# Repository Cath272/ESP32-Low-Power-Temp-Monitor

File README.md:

# ESP32 Low Power Temp Monitor

## Introduction
ESP32 Low Power Temp Monitor is an ESP32 C6 based low power Temperature and Humidity Monitor that aims to have a device that is very efficent and doen't need charging.
## General description
The device reads the temperature, relative humidity and barometric pressure  and displays it on an 4.2 inch Epaper Display, alonside the current date and time.
The device is awake just for a few seconds as it reads the tempereature and displays it and then goes to sleep. It performs a reading every minute.
One a day it connects to WiFi and checks the current time to sync up with an NTP server to account for Daylight saving time and potential drifts in the internal esp32 real time clock.

In the project files you may find ESP32-C3 instead of ESP32-C6. I named it wrong when i created the project. The issue is just the file names, the footprints are correct and use a C6.
The TPL5111 is currenly does not work properly so i emulated it in software using the esp32 deep sleep.

### Block diagram

## Hardware Design
### ESP32 C6 Wroom 1 Module
This project is based around a ESP32 C6 Wroom 1 Module that incorporates a RISC-V single-core microprocessor with 4MB of flash, WiFi 6 and Zigbee
### TPS63020
The TPS63020 is High Efficiency Single Inductor Buck-Boost Converter, used for  converting the 5v from usb or the Li-ion battery voltage(3.0v to 4.2v) to a very stable 3.3V for the Microcontroller and the epaper display. The main advantage of this ic is its low operating quiescent current: 25 μA; and it's low cost:0.55€
### BME280
The BME280 is a digital humidity, pressure and temperature sensor.
### 4.2 Inch Epaper Display 
GDEY042Z98 Tri color (Black, White and Red) Epaper display using a SSD1683 driver chip, the main benefit of this display is its big size (4.2 inch) and very good price for an Epaper display (around 10€)
### TPL5111
The TPL5111 is a Nano Power System timer for power gating. It is used to turn on the esp32 every minute to read the temperature
### MCP7381
The MCP7381 is an integrated Li-ion cell battery controller 
### Li-ion 250MAh battery
Small 250Mah generic Li-ion cell with protection, used because of its small size
### Solar Panel
Generic 1W 5V Solar panel 

## Schematic
[Schematic](PCB/ESP32%20%20C3%20Zigbee%20Temp/ESP32%20%20C3%20Zigbee%20Temp.pdf)
## Bill of Materials

| Component           |         Image                                                                                         |         Model  |           Pcs | Price           | 
| -------------       |                                                                                        -------------  | -------------  | ------------- | --------------- |
| ESP32-C6-WROOM-1-N8  |          | ESP32-C6-WROOM-1-N8 | 1             | € 4.91          |
|Buck Boost Coverter  |        |   TPS63020     | 1             | € 0.52          | 
| TPL5111        |             | TPL5111         | 1             | € 0.47       |     
| BME280        |             | BME280         | 1             | € 2.78      |
| MCP7381        |             | MCP7381         | 1             | € 0.84      |
| Solar Panel        |             | 5V 1W Solar Panel         | 1             | € 2.23       |
| 4.2 Inch Epaper Display |             | GDEY042Z98         | 1             | € 11.64       |

## PCB

## Case and 3d design

The case was make using autocad and exported to stl
The stl files can be found in the 3D Parts folder

The gerber production zip file can be found in the Production folder
## Software Design

The device wakes up, connect to wifi on the first boot, reads the time from an NTP server, and then for the next 24 hours it just reads the temperature and displays it. The time is kept in a register while the esp sleeps and increments it on every boot. Every 24 hours it connect to Wifi to check the time again for accuracy.
The program can be found in the Project_Code folder

### Display
The program is based around the [GxEPD2](https://github.com/ZinggJM/GxEPD2) libary for interfacing with the Epaper display,   

### Fonts
The font used in this project is Roboto with 2 diffrent font sizes: 16pt for the time, date, altitude and barometric pressure and 48pt for the Temeprature and relative humidity
The font were converted from True Type to Adafruit's GFX Font format (also used by GxEPD2 as it is based on Adafruit GFX) using the [ttf2gfx utility](https://github.com/Pconti31/TTF2GFX)

### BME280
Adafruit_BME280 for the BME280 sensor
### Time 
For time i used 4 libraries: 
- esp_timer (esp_idf library) to get the execution time of the code 
- [ESP32Time](https://github.com/fbiego/ESP32Time) for keeeping the time and displaying it in a C style format on the display
- [ezTime](https://github.com/ropg/ezTime) for getting the time from an NTP server, the time is region based in this library and i used it to avoid the problem of keeping track of daylight savings

## Results

## Resources
- [ESP32Time](https://github.com/fbiego/ESP32Time)
- [ttf2gfx utility](https://github.com/Pconti31/TTF2GFX)
- [ezTime](https://github.com/ropg/ezTime)
- [GxEPD2](https://github.com/ZinggJM/GxEPD2)

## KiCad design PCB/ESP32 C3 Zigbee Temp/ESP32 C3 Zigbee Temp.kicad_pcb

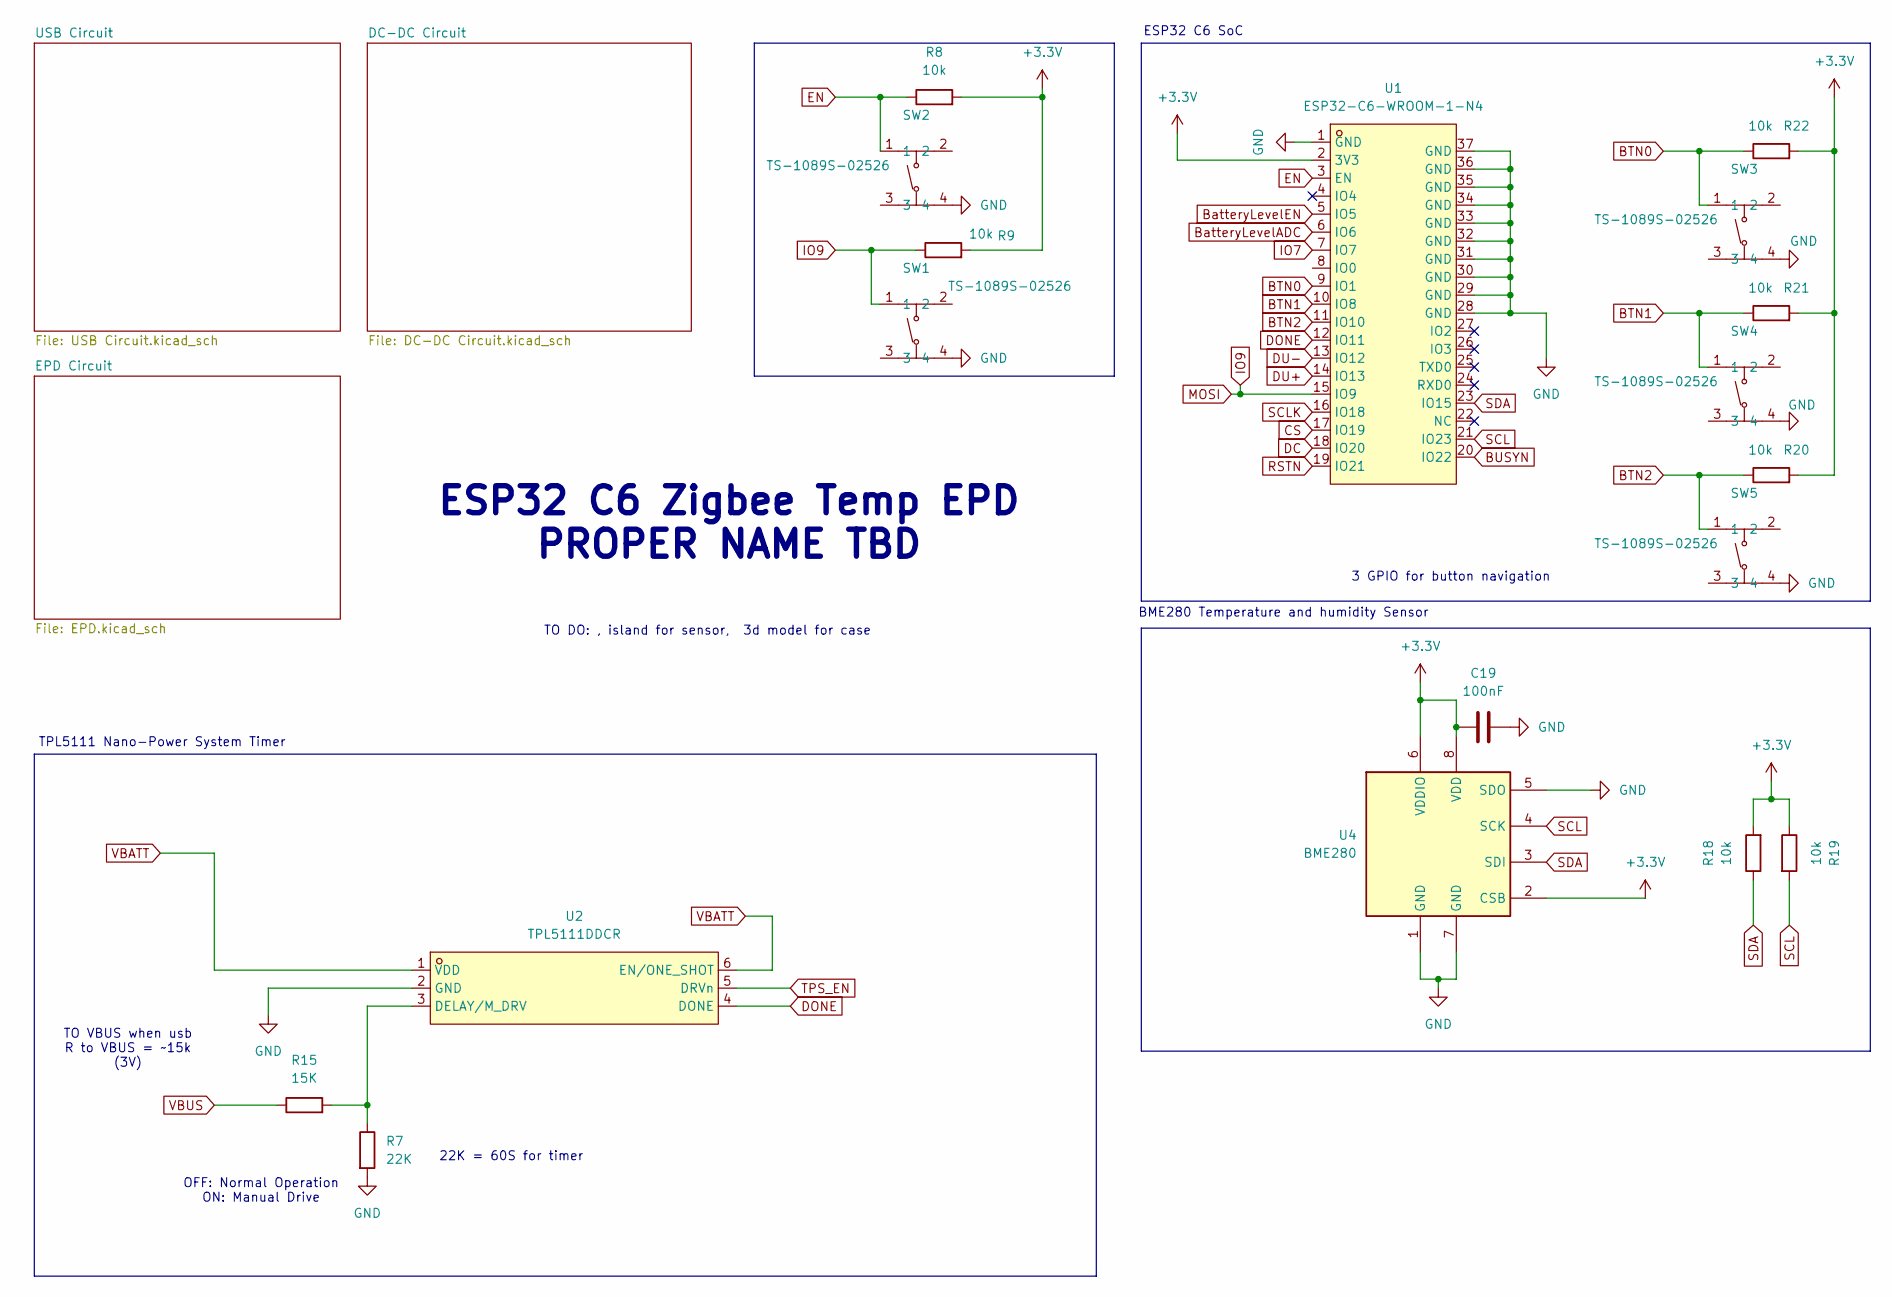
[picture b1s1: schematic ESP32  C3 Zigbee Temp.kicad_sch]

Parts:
C19: 100nF; C_0402_1005Metric
R7: 22K; R_0402_1005Metric
R8, R9, R18, R19, R20, R21, R22: 10k; R_0402_1005Metric
R15: 15K; R_0402_1005Metric
SW1, SW2, SW3, SW4, SW5: TS-1089S-02526; SW-SMD_4P-L4.2-W3.3-P2.15-LS5.1; LCSC Part C455282
U1: ESP32-C6-WROOM-1-N4; WIRELM-SMD_ESP32-C6-WROOM-1; LCSC Part C6034714
U2: TPL5111DDCR; TSOT-23-6_L2.9-W1.6-P0.95-LS2.8-BL; LCSC Part C2870554
U4: BME280; Bosch_LGA-8_2.5x2.5mm_P0.65mm_ClockwisePinNumbering

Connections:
+3.3V: C19.1, R8.2, R9.2, R18.2, R19.1, R20.2, R21.2, R22.2, U1.2 (3V3), U4.2 (CSB), U4.6 (VDDIO), U4.8 (VDD); also elsewhere on the board
BTN0: R22.1, SW3.1, U1.9 (IO1)
BTN1: R21.1, SW4.1, U1.10 (IO8)
BTN2: R20.1, SW5.1, U1.11 (IO10)
BUSYN: U1.20 (IO22); also elsewhere on the board
BatteryLevelADC: U1.6 (IO6); also elsewhere on the board
BatteryLevelEN: U1.5 (IO5); also elsewhere on the board
CS: U1.17 (IO19); also elsewhere on the board
DC: U1.18 (IO20); also elsewhere on the board
DONE: U1.12 (IO11), U2.4 (DONE)
DU+: U1.14 (IO13); also elsewhere on the board
DU-: U1.13 (IO12); also elsewhere on the board
EN: R8.1, SW2.1, U1.3 (EN)
GND: C19.2, R7.2, SW1.4, SW2.4, SW3.4, SW4.4, SW5.4, U1.1 (GND), U1.28 (GND), U1.29 (GND), U1.30 (GND), U1.31 (GND), U1.32 (GND), U1.33 (GND), U1.34 (GND), U1.35 (GND), U1.36 (GND), U1.37 (GND), U2.2 (GND), U4.1 (GND), U4.5 (SDO), U4.7 (GND); also elsewhere on the board
IO7: U1.7 (IO7); also elsewhere on the board
IO9: R9.1, SW1.1, U1.15 (IO9); also elsewhere on the board
unnamed: R7.1, R15.2, U2.3 (DELAY/M_DRV)
RSTN: U1.19 (IO21); also elsewhere on the board
SCL: R19.2, U1.21 (IO23), U4.4 (SCK)
SCLK: U1.16 (IO18); also elsewhere on the board
SDA: R18.1, U1.23 (IO15), U4.3 (SDI)
TPS_EN: U2.5 (DRVn); also elsewhere on the board
VBATT: U2.1 (VDD), U2.6 (EN/ONE_SHOT); also elsewhere on the board
VBUS: R15.1; also elsewhere on the board

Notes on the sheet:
ESP32 C6 SoC
OFF: Normal Operation ON: Manual Drive
3 GPIO for button navigation
TO DO: , island for sensor, 3d model for case
TO VBUS when usb R to VBUS = ~15k (3V)
TPL5111 Nano-Power System Timer
ESP32 C6 Zigbee Temp EPD PROPER NAME TBD
22K = 60S for timer
BME280 Temperature and humidity Sensor

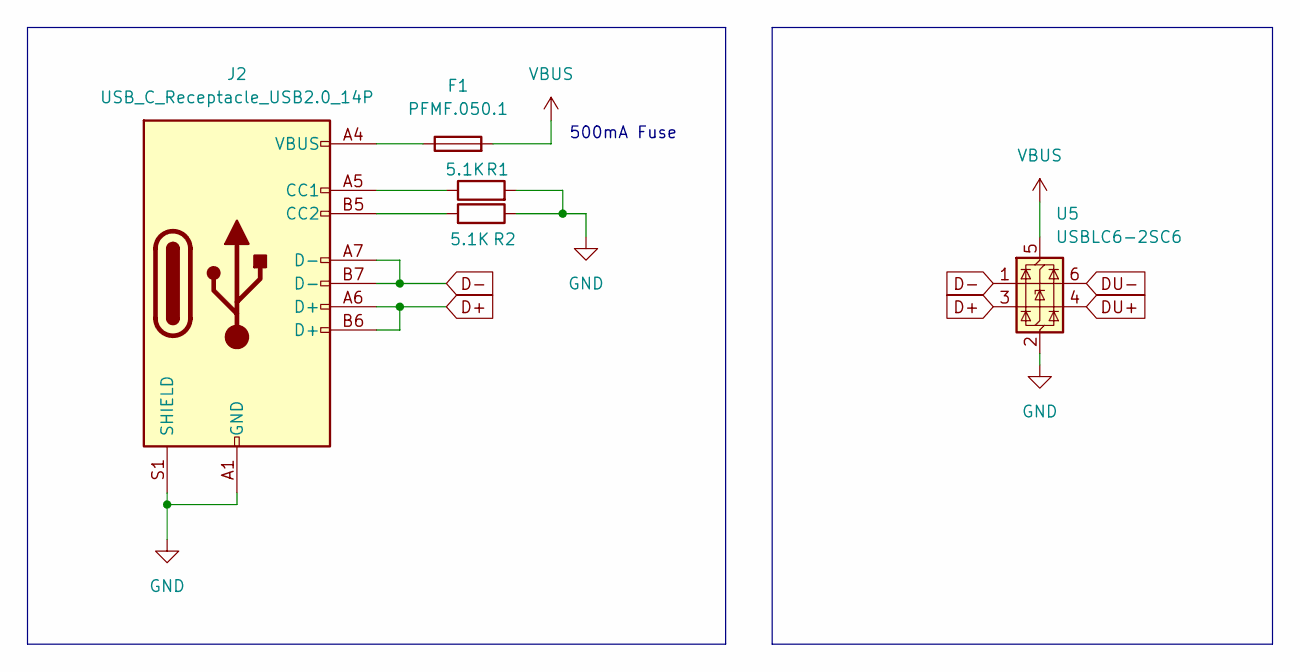
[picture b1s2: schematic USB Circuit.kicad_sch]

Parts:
F1: PFMF.050.1; Fuse_1812_4532Metric
J2: USB_C_Receptacle_USB2.0_14P; USB_C_Receptacle_GCT_USB4110
R1, R2: 5.1K; R_0402_1005Metric
U5: USBLC6-2SC6; SOT-23-6

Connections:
D+: J2.A6 (D+), J2.B6 (D+), U5.3 (I/O2)
D-: J2.A7 (D-), J2.B7 (D-), U5.1 (I/O1)
DU+: U5.4 (I/O2); also elsewhere on the board
DU-: U5.6 (I/O1); also elsewhere on the board
GND: J2.A1 (GND), J2.A12 (GND), J2.B1 (GND), J2.B12 (GND), J2.S1 (SHIELD), R1.2, R2.1, U5.2 (GND); also elsewhere on the board
unnamed: F1.1, J2.A4 (VBUS), J2.A9 (VBUS), J2.B4 (VBUS), J2.B9 (VBUS)
unnamed: J2.A5 (CC1), R1.1
unnamed: J2.B5 (CC2), R2.2
VBUS: F1.2, U5.5 (VBUS); also elsewhere on the board

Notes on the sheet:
500mA Fuse

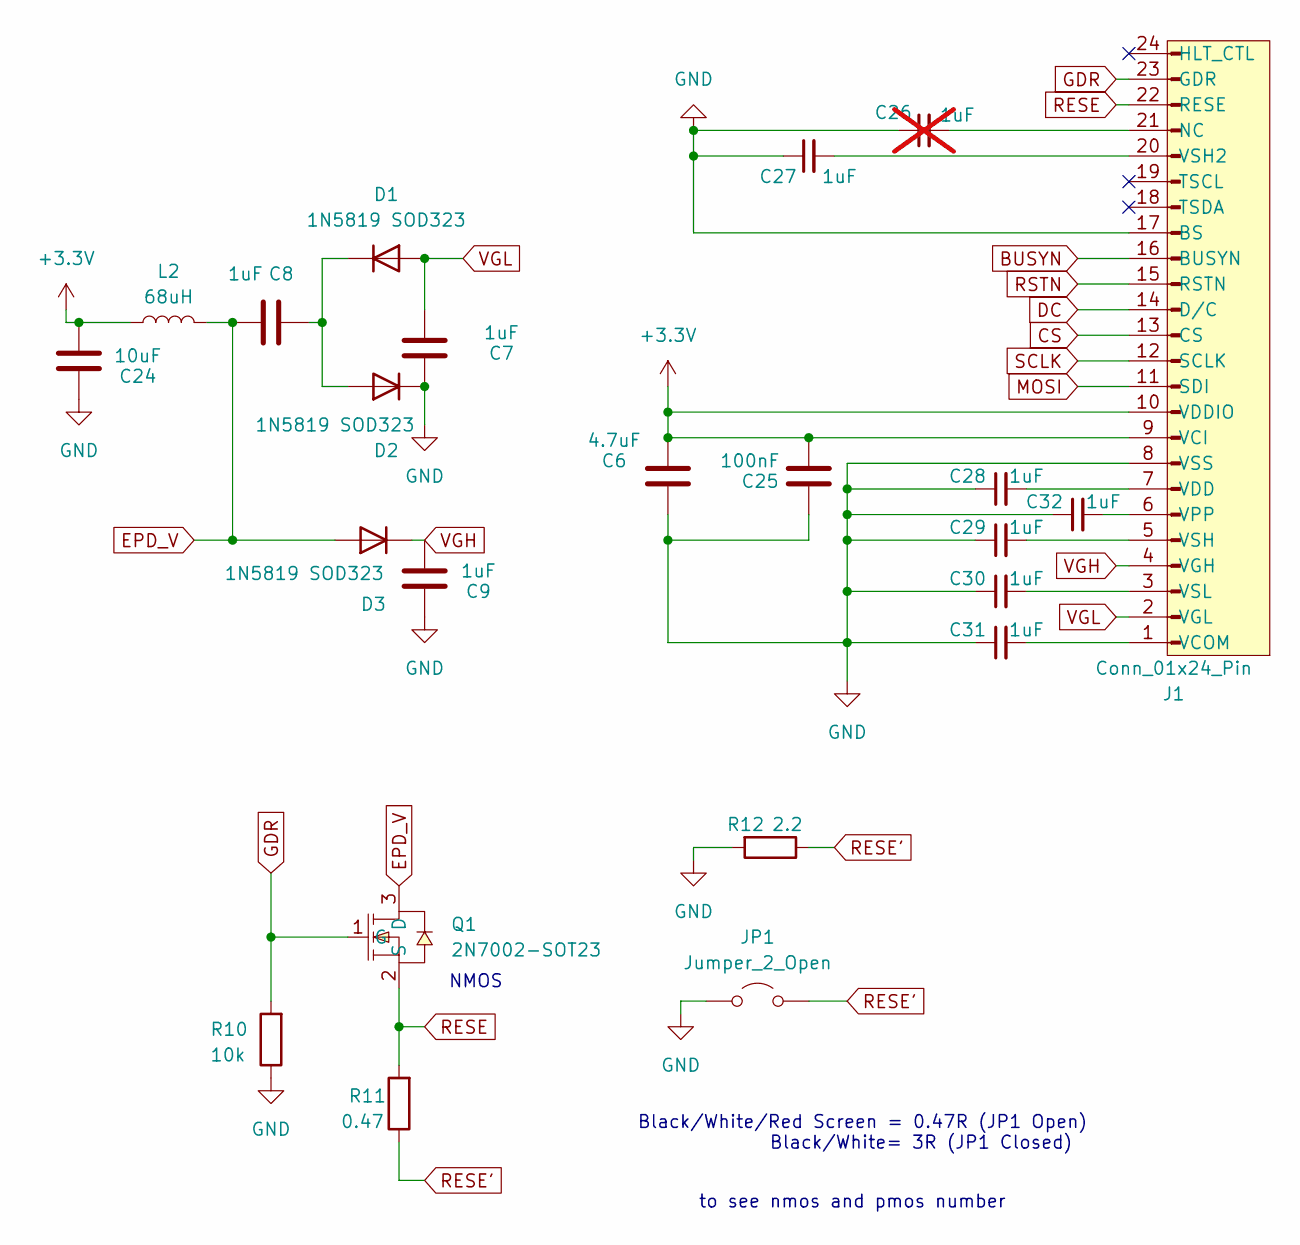
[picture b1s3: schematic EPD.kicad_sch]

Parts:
C6: 4.7uF; C_0805_2012Metric
C7, C8, C9, C27, C28, C29, C30, C31, C32: 1uF; C_0603_1608Metric
C24: 10uF; C_0805_2012Metric
C25: 100nF; C_0402_1005Metric
C26: 1uF; C_0603_1608Metric; not fitted
D1, D2, D3: 1N5819 SOD323; D_SOD-323
J1: Conn_01x24_Pin; MOLEX_5034802400
JP1: Jumper_2_Open; SolderJumper-2_P1.3mm_Open_TrianglePad1.0x1.5mm
L2: 68uH; L_APV_ANR4030
Q1: 2N7002-SOT23; SOT-23_L2.9-W1.3-P1.90-LS2.4-BR; LCSC Part C332103
R10: 10k; R_0402_1005Metric
R11: 0.47; R_0402_1005Metric
R12: 2.2; R_0402_1005Metric

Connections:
+3.3V: C6.2, C24.2, C25.2, J1.9 (VCI), J1.10 (VDDIO), L2.1; also elsewhere on the board
BUSYN: J1.16 (BUSYN); also elsewhere on the board
CS: J1.13 (CS); also elsewhere on the board
DC: J1.14 (D/C); also elsewhere on the board
EPD_V: C8.2, D3.2 (A), L2.2, Q1.3 (D)
GDR: J1.23 (GDR), Q1.1 (G), R10.2
GND: C6.1, C7.1, C9.1, C24.1, C25.1, C26.1, C27.1, C28.1, C29.1, C30.1, C31.1, C32.1, D2.1 (K), J1.8 (VSS), J1.17 (BS), JP1.1 (A), R10.1, R12.2; also elsewhere on the board
IO9: J1.11 (SDI); also elsewhere on the board
unnamed: C8.1, D1.1 (K), D2.2 (A)
unnamed: C26.2, J1.21 (NC)
unnamed: C31.2, J1.1 (VCOM)
unnamed: C28.2, J1.7 (VDD)
unnamed: C32.2, J1.6 (VPP)
unnamed: C27.2, J1.20 (VSH2)
unnamed: C29.2, J1.5 (VSH)
unnamed: C30.2, J1.3 (VSL)
RESE: J1.22 (RESE), Q1.2 (S), R11.2
RESE': JP1.2 (B), R11.1, R12.1
RSTN: J1.15 (RSTN); also elsewhere on the board
SCLK: J1.12 (SCLK); also elsewhere on the board
VGH: C9.2, D3.1 (K), J1.4 (VGH)
VGL: C7.2, D1.2 (A), J1.2 (VGL)

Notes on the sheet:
to see nmos and pmos number
NMOS
Black/White/Red Screen = 0.47R (JP1 Open) Black/White= 3R (JP1 Closed)

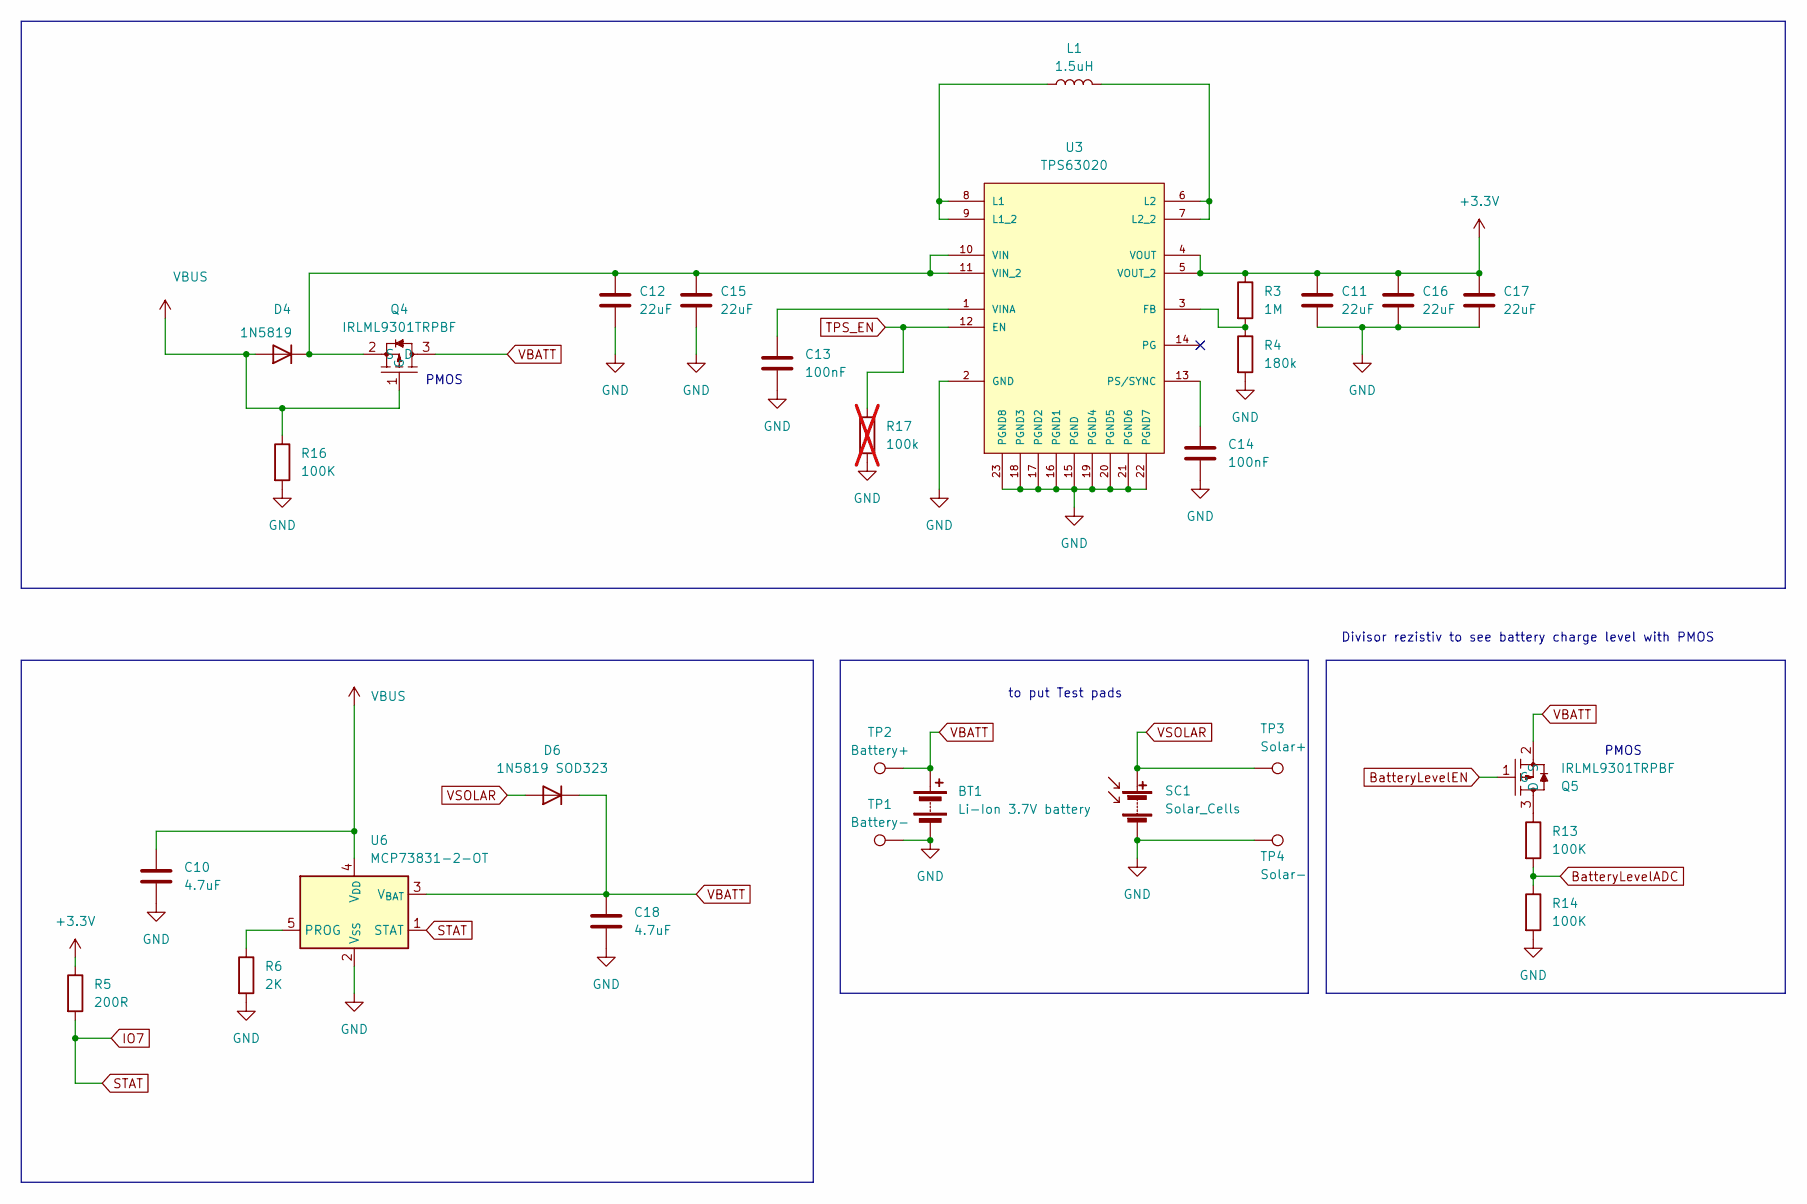
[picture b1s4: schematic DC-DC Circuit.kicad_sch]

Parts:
BT1: Li-Ion 3.7V battery
C10, C18: 4.7uF; C_0805_2012Metric
C11, C12, C15, C16, C17: 22uF; C_0805_2012Metric
C13, C14: 100nF; C_0402_1005Metric
D4: 1N5819; D_SOD-323
D6: 1N5819 SOD323; D_SOD-323
L1: 1.5uH; L_APV_ANR4030
Q4, Q5: IRLML9301TRPBF; SOT-23_L2.9-W1.3-P1.90-LS2.4-BR; LCSC Part C82056
R3: 1M; R_0402_1005Metric
R4: 180k; R_0402_1005Metric
R5: 200R; R_0402_1005Metric
R6: 2K; R_0402_1005Metric
R13, R14, R16: 100K; R_0402_1005Metric
R17: 100k; R_0402_1005Metric; not fitted
SC1: Solar_Cells
TP1: Battery-; TestPoint_Pad_2.0x2.0mm
TP2: Battery+; TestPoint_Pad_2.0x2.0mm
TP3: Solar+; TestPoint_Pad_2.0x2.0mm
TP4: Solar-; TestPoint_Pad_2.0x2.0mm
U3: TPS63020; VSON-14_L4.0-W3.0-P0.50-BL-EP_TI_DSJ
U6: MCP73831-2-OT; SOT-23-5

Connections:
+3.3V: C11.1, C16.1, C17.1, R3.1, R5.1, U3.4 (VOUT), U3.5 (VOUT_2); also elsewhere on the board
BatteryLevelADC: R13.2, R14.1; also elsewhere on the board
BatteryLevelEN: Q5.1 (G); also elsewhere on the board
GND: BT1.2 (-), C10.2, C11.2, C12.2, C13.2, C14.2, C15.2, C16.2, C17.2, C18.2, R4.2, R6.2, R14.2, R16.2, R17.2, SC1.2 (-), TP1.1, TP4.1, U3.2 (GND), U3.15 (PGND), U3.16 (PGND1), U3.17 (PGND2), U3.18 (PGND3), U3.19 (PGND4), U3.20 (PGND5), U3.21 (PGND6), U3.22 (PGND7), U3.23 (PGND8), U6.2 (V_{SS}); also elsewhere on the board
IO7: R5.2, U6.1 (STAT); also elsewhere on the board
unnamed: C12.1, C15.1, D4.1 (K), Q4.2 (S), U3.10 (VIN), U3.11 (VIN_2)
unnamed: Q5.3 (D), R13.1
unnamed: R3.2, R4.1, U3.3 (FB)
unnamed: L1.1, U3.8 (L1), U3.9 (L1_2)
unnamed: L1.2, U3.6 (L2), U3.7 (L2_2)
unnamed: C14.1, U3.13 (PS/SYNC)
unnamed: C13.1, U3.1 (VINA)
unnamed: R6.1, U6.5 (PROG)
TPS_EN: R17.1, U3.12 (EN); also elsewhere on the board
VBATT: BT1.1 (+), C18.1, D6.1 (K), Q4.3 (D), Q5.2 (S), TP2.1, U6.3 (V_{BAT}); also elsewhere on the board
VBUS: C10.1, D4.2 (A), Q4.1 (G), R16.1, U6.4 (V_{DD}); also elsewhere on the board
VSOLAR: D6.2 (A), SC1.1 (+), TP3.1

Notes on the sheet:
Divisor rezistiv to see battery charge level with PMOS
PMOS
to put Test pads
PMOS

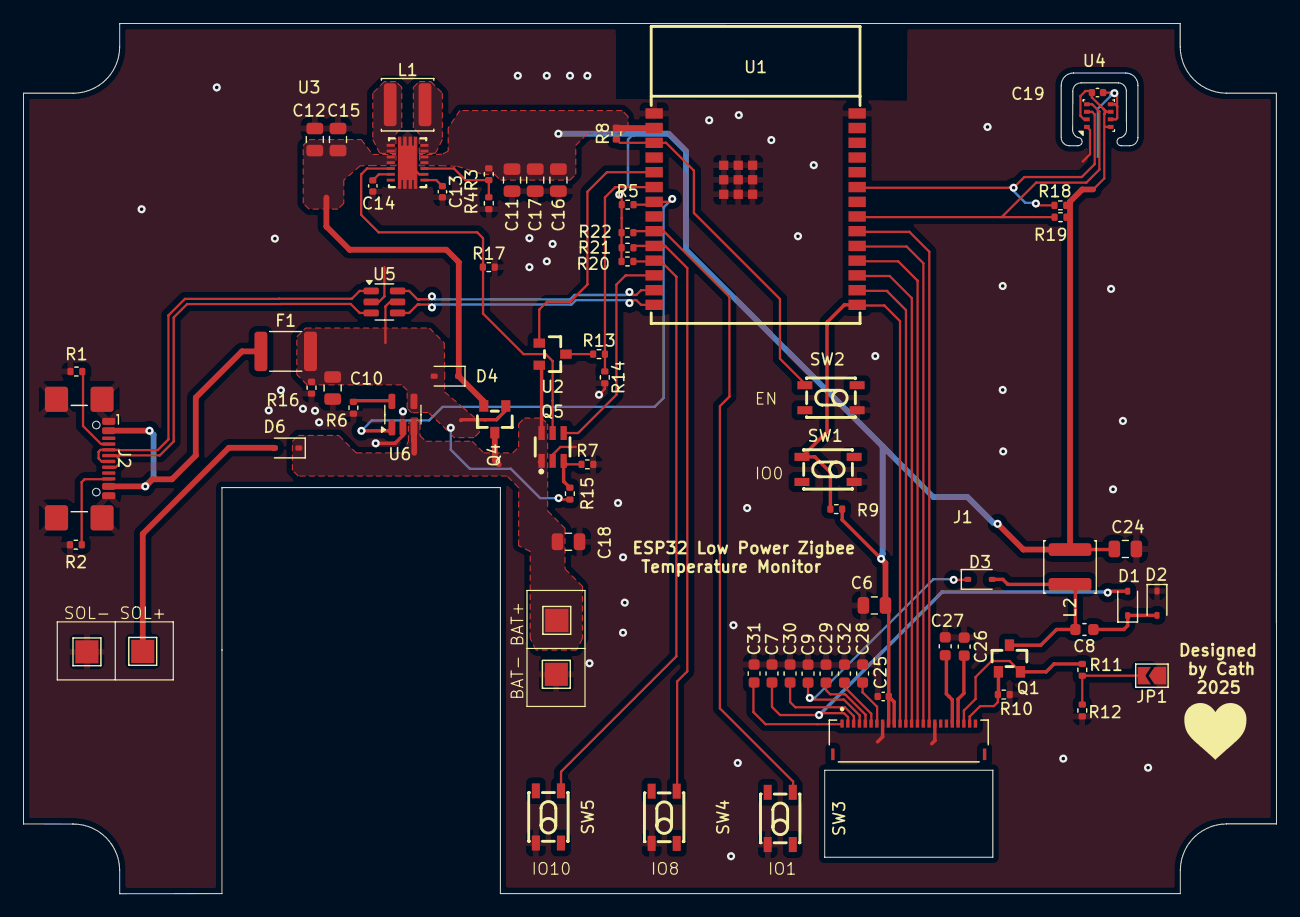
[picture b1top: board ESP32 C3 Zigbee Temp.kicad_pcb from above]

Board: 2 copper layers, 108.0 x 75.0 mm, 74 parts (0 on the bottom side), 52 nets.
